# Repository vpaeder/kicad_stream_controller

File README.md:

# Fichiers KiCad pour mon stream twitch d'électronique absconse
Pour en savoir plus, venez me dire coucou sur https://twitch.tv/cannetier .

Le but du projet étant mouvant, il risque que ça meuve. A ce stade néanmoins, je me dirige vers un petit boitier pour contrôler <insérer votre choix ici> avec les fonctionalités suivantes :
 - connection USB ou sans fil par bluetooth ou wifi
 - écran tactile
 - dans la v1, deux potentiomètres intégrés (la v2 devrait être modulaire)
 - batterie intégrée
 - coeur ESP32
 - abordable (pour l'instant environ 75 euros avec le boitier et les frais de port, pour un prototype en 1 exemplaire)

J'en suis à la v1 qui est censée être assez facile à fabriquer.
La v2 devrait être modulaire avec la possibilité de rajouter des blocs en chaîne sur les côtés. J'ai déjà créé un repo avec les fichiers OpenSCAD pour le boitier ici : https://github.com/vpaeder/openscad_modbox

Voilà quelques images pour donner une idée du résultat :

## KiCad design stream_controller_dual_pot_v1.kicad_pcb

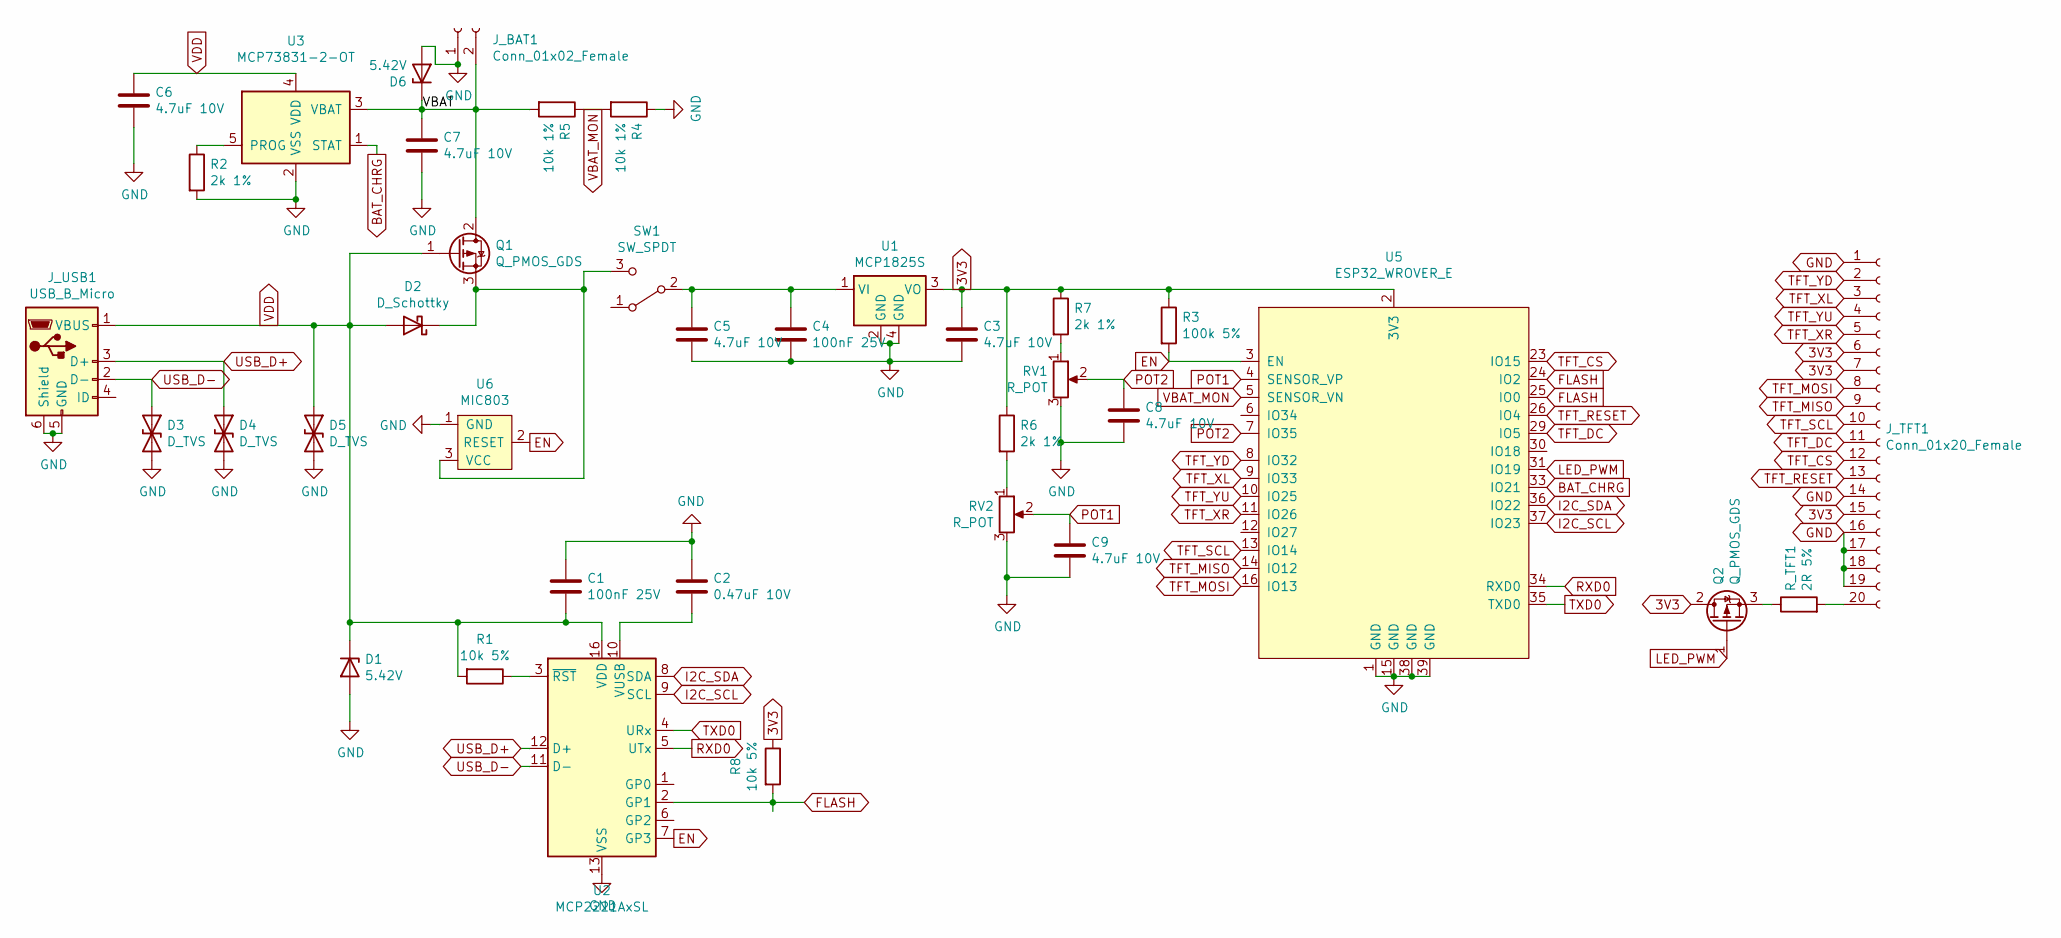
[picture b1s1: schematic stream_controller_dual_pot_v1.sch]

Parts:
C1, C4: 100nF 25V; C_0402_1005Metric_Pad0.74x0.62mm_HandSolder
C2: 0.47uF 10V; C_0402_1005Metric_Pad0.74x0.62mm_HandSolder
C3, C5, C6, C7, C8, C9: 4.7uF 10V; C_0402_1005Metric_Pad0.74x0.62mm_HandSolder
D1, D6: 5.42V; D_SOD-323F
D2: D_Schottky; D_SMA
D3, D4, D5: D_TVS; D_SOD-523
J_BAT1: Conn_01x02_Female; PinHeader_1x02_P2.54mm_Vertical
J_TFT1: Conn_01x20_Female; FFC3B11-20-T
J_USB1: USB_B_Micro; 10118193-0001LF
Q1: Q_PMOS_GDS; Diodes_DFN1006-3
Q2: Q_PMOS_GDS; SOT-23
R1, R8: 10k 5%; R_0402_1005Metric_Pad0.72x0.64mm_HandSolder
R2, R6, R7: 2k 1%; R_0402_1005Metric_Pad0.72x0.64mm_HandSolder
R3: 100k 5%; R_0402_1005Metric_Pad0.72x0.64mm_HandSolder
R4, R5: 10k 1%; R_0402_1005Metric_Pad0.72x0.64mm_HandSolder
RV1, RV2: R_POT; P160KNPD-4FC20B
R_TFT1: 2R 5%; R_0402_1005Metric_Pad0.72x0.64mm_HandSolder
SW1: SW_SPDT; GF-126-0331
U1: MCP1825S; SOT-223
U2: MCP2221AxSL; QFN-16-1EP_4x4mm_P0.65mm_EP2.5x2.5mm
U3: MCP73831-2-OT; SOT-23-5
U5: ESP32_WROVER_E; ESP32-WROVER-E
U6: MIC803; SOT-23

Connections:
3V3: C3.1, J_TFT1.6, J_TFT1.7, J_TFT1.15, Q2.2 (D), R3.1, R6.1, R7.1, R8.1, U1.3 (VO), U5.2 (3V3)
/VBAT: C7.1, D6.1 (K), J_BAT1.2, Q1.2 (D), R5.2, U3.3 (VBAT)
BAT_CHRG: U3.1 (STAT), U5.33 (IO21)
EN: R3.2, U2.7 (GP3), U5.3 (EN), U6.2 (RESET)
FLASH: R8.2, U2.2 (GP1), U5.24 (IO2), U5.25 (IO0)
GND: C1.1, C2.1, C3.2, C4.2, C5.2, C6.2, C7.2, C8.2, C9.2, D1.2 (A), D3.2 (A2), D4.2 (A2), D5.2 (A2), D6.2 (A), J_BAT1.1, J_TFT1.1, J_TFT1.14, J_TFT1.16, J_TFT1.17, J_TFT1.18, J_TFT1.19, J_TFT1.NC, J_USB1.5 (GND), J_USB1.6 (Shield), R2.2, R4.1, RV1.3, RV2.3, U1.2 (GND), U1.4 (GND), U2.13 (VSS), U3.2 (VSS), U5.1 (GND), U5.15 (GND), U5.38 (GND), U5.39 (GND), U6.1 (GND)
I2C_SCL: U2.9 (SCL), U5.37 (IO23)
I2C_SDA: U2.8 (SDA), U5.36 (IO22)
LED_PWM: Q2.1 (G), U5.31 (IO19)
unnamed: C2.2, U2.10 (VUSB)
unnamed: C4.1, C5.1, SW1.2 (B), U1.1 (VI)
unnamed: D2.1 (K), Q1.3 (S), SW1.3 (C), U6.3 (VCC)
unnamed: J_TFT1.20, R_TFT1.2
unnamed: Q2.3 (S), R_TFT1.1
unnamed: R1.1, U2.3 (~RST)
unnamed: R2.1, U3.5 (PROG)
unnamed: R6.2, RV2.1
unnamed: R7.2, RV1.1
POT1: C9.1, RV2.2, U5.4 (SENSOR_VP)
POT2: C8.1, RV1.2, U5.7 (IO35)
RXD0: U2.5 (UTx), U5.34 (RXD0)
TFT_CS: J_TFT1.12, U5.23 (IO15)
TFT_DC: J_TFT1.11, U5.29 (IO5)
TFT_MISO: J_TFT1.9, U5.14 (IO12)
TFT_MOSI: J_TFT1.8, U5.16 (IO13)
TFT_RESET: J_TFT1.13, U5.26 (IO4)
TFT_SCL: J_TFT1.10, U5.13 (IO14)
TFT_XL: J_TFT1.3, U5.9 (IO33)
TFT_XR: J_TFT1.5, U5.11 (IO26)
TFT_YD: J_TFT1.2, U5.8 (IO32)
TFT_YU: J_TFT1.4, U5.10 (IO25)
TXD0: U2.4 (URx), U5.35 (TXD0)
USB_D+: D4.1 (A1), J_USB1.3 (D+), U2.12 (D+)
USB_D-: D3.1 (A1), J_USB1.2 (D-), U2.11 (D-)
VBAT_MON: R4.2, R5.1, U5.5 (SENSOR_VN)
VDD: C1.2, C6.1, D1.1 (K), D2.2 (A), D5.1 (A1), J_USB1.1 (VBUS), Q1.1 (G), R1.2, U2.16 (VDD), U3.4 (VDD)

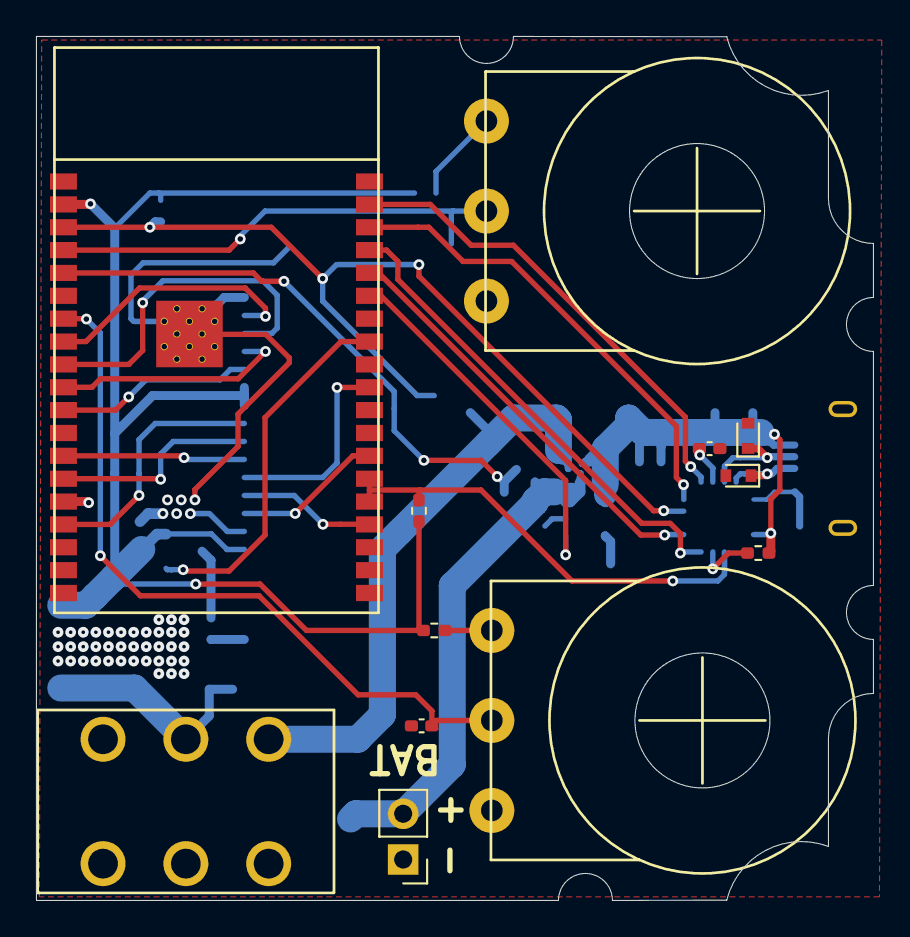
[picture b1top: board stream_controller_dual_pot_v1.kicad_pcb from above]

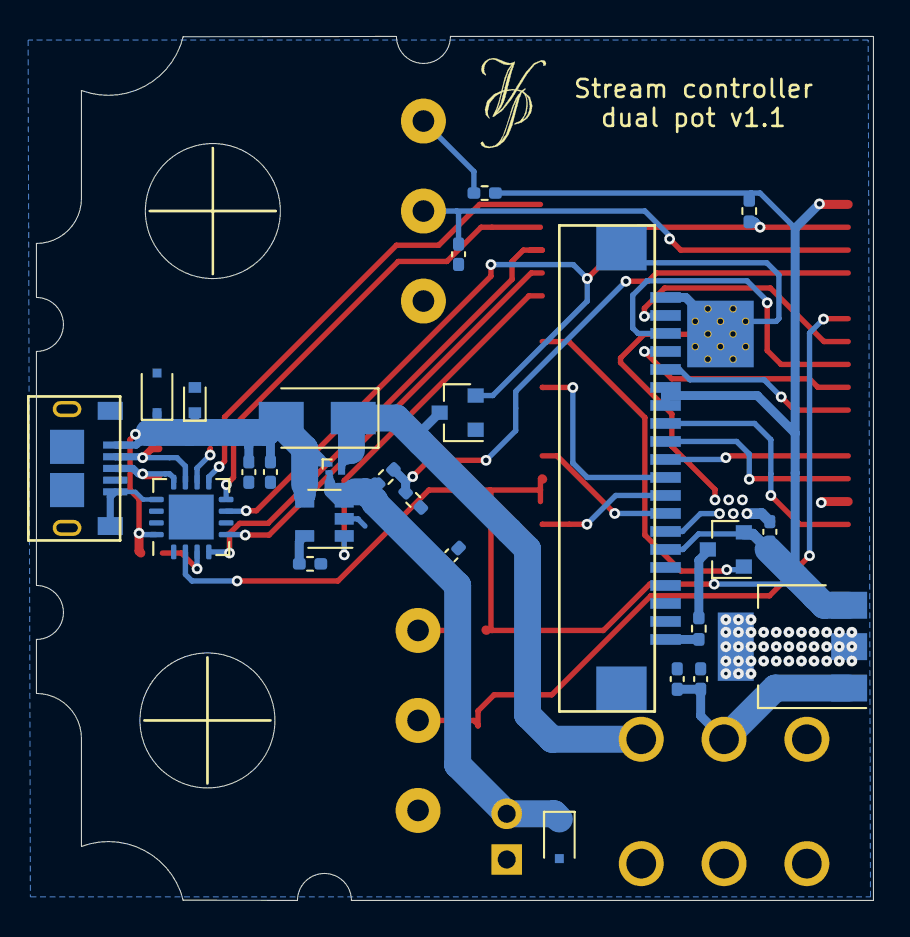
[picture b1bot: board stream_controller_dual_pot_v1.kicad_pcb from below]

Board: 2 copper layers, 46.5 x 48.0 mm, 37 parts (25 on the bottom side), 36 nets.

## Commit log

2021-05-04 bug UART corrigé
2021-05-06 Correction IO0 forcé à 1
    Si IO0 n'est pas haut au démarrage, l'ESP32 se met en mode flash. Quand non-connecté par USB, IO0 doit être forcé à 1, car le contrôleur USB n'est pas alimenté.
2021-05-06 Create LICENSE
2021-05-06 Ajout contrôle pin EN par contrôleur USB
2021-05-06 Ajout BOM
2021-05-06 Ajout d'images
2021-05-06 Correction images
2021-05-09 Changements divers
    Modifications :
    - toutes les entrées analogiques sur ADC1, car ADC2 ne peut pas être utilisé si le WiFi est actif
    - lecture de l'écran tactile déplacée sur pattes 8, 9, 10 et 11, car les pattes 4, 5, 6 et 7 sont en lecture seule
    - changement du transistor pour le contrôle de la luminosité de l'écran
2021-05-10 Corrections et ajouts
    Corrigé : strapping pin 2 connectée au même signal FLASH que pin 0
    Ajouté : I2C entre uC et contrôleur USB
